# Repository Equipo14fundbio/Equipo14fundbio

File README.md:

### Hi there 👋

<!--
**Equipo14fundbio/Equipo14fundbio** is a ✨ _special_ ✨ repository because its `README.md` (this file) appears on your GitHub profile.

Here are some ideas to get you started:

- 🔭 I’m currently working on ...
- 🌱 I’m currently learning ...
- 👯 I’m looking to collaborate on ...
- 🤔 I’m looking for help with ...
- 💬 Ask me about ...
- 📫 How to reach me: ...
- 😄 Pronouns: ...
- ⚡ Fun fact: ...
-->

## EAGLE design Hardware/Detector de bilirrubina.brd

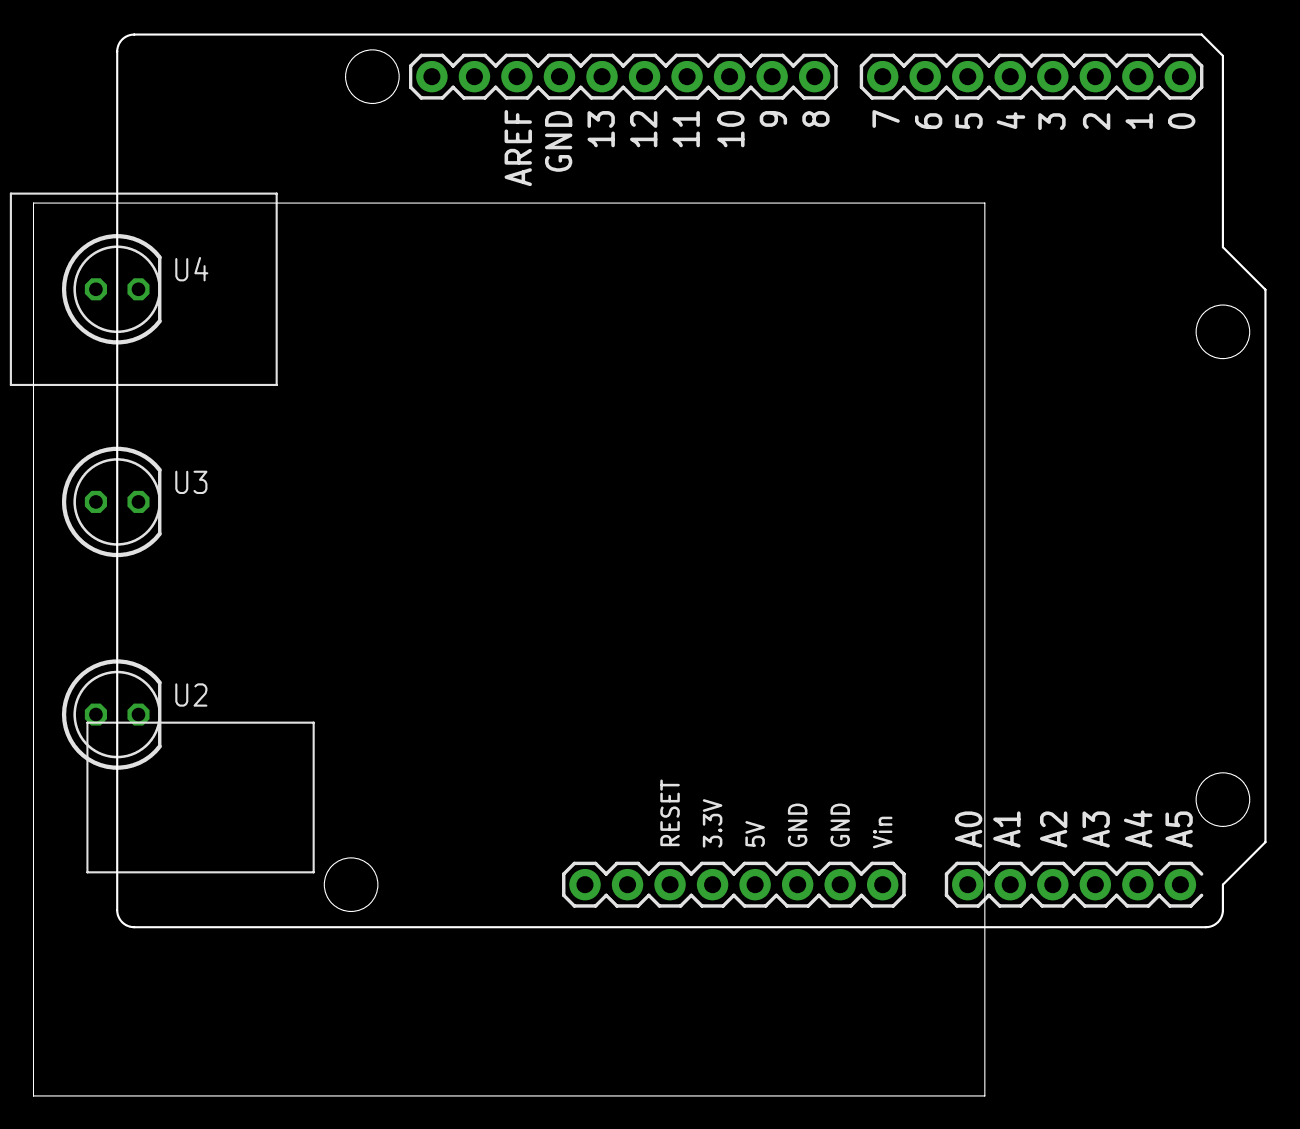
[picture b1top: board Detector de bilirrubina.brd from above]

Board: 2 copper layers, 73.5 x 63.3 mm, 4 parts (0 on the bottom side), 4 nets, no tracks yet.

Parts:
U1: ARDUINO_UNO
U2, U3, U4: LED5MM

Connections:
unnamed: U1.A0, U2.A
unnamed: U1.A1, U3.A
unnamed: U1.GND., U2.K, U3.K, U4.K
unnamed: U1.A2, U4.A

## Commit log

2021-11-20 Create ValueAdapter
